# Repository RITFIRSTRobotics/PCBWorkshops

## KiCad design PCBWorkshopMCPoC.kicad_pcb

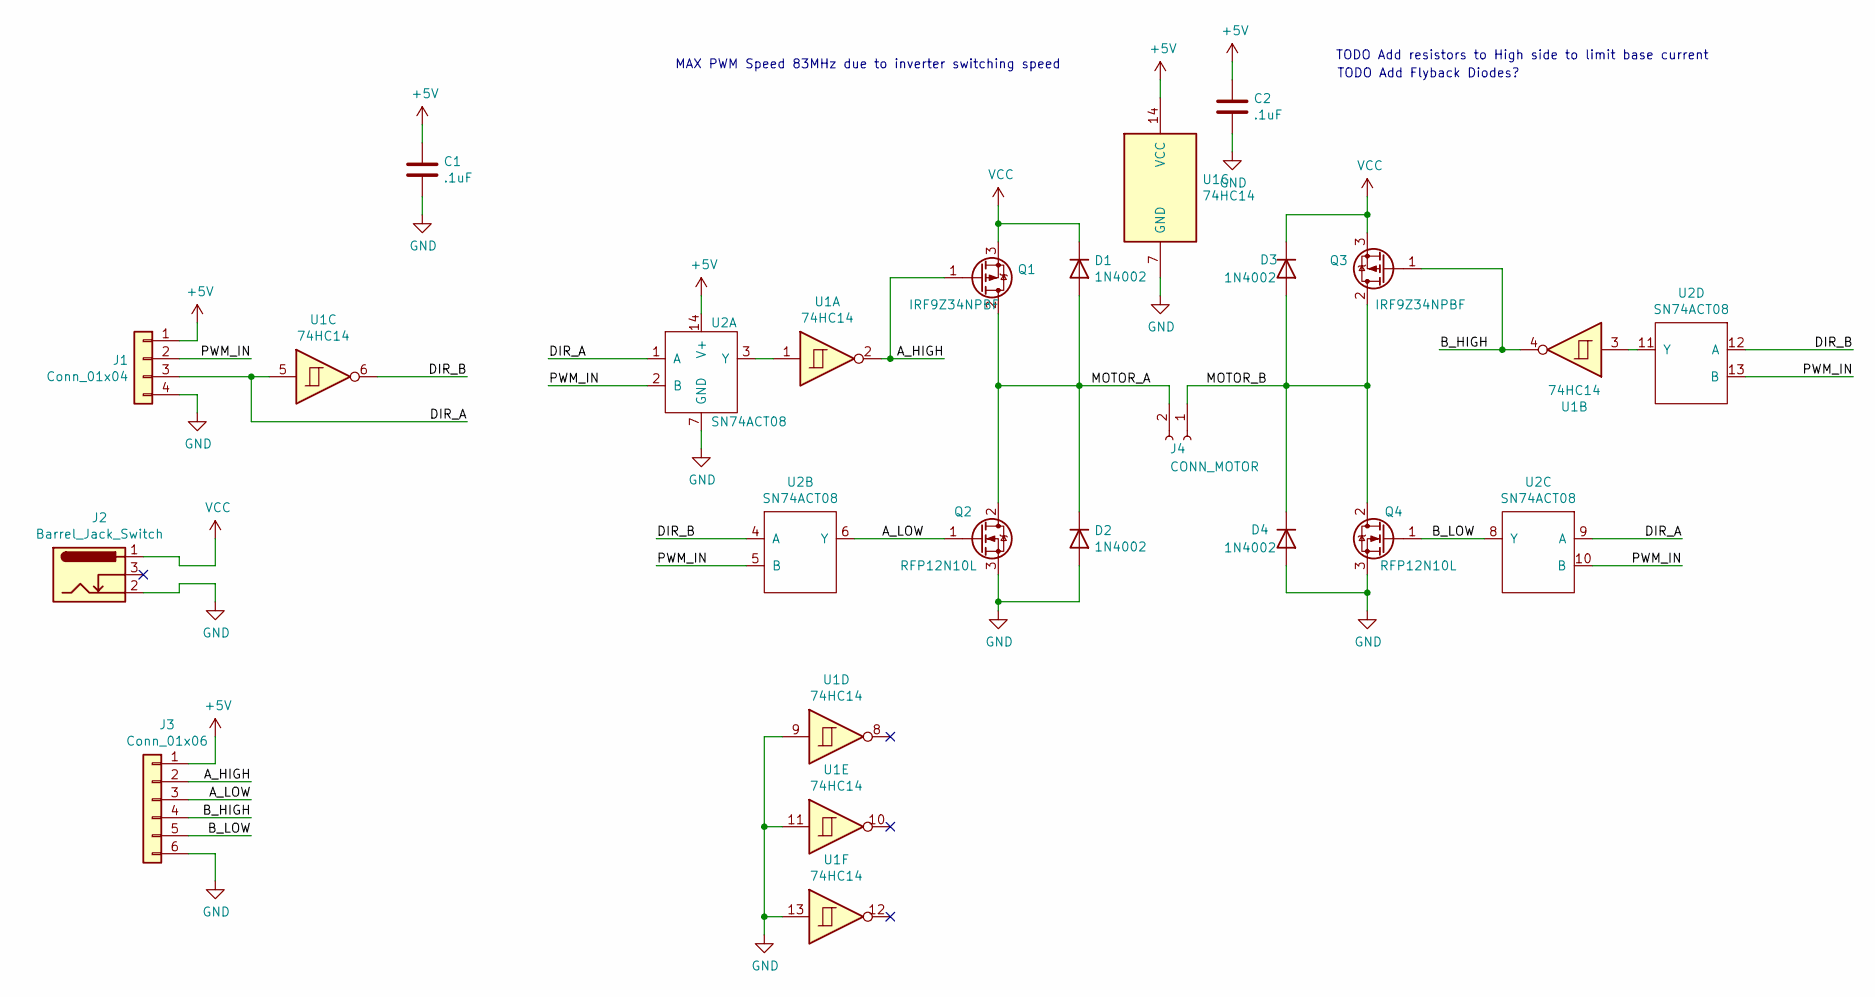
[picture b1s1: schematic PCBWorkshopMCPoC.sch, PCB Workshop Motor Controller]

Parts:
C1, C2: .1uF; C_Disc_D5.0mm_W2.5mm_P2.50mm
D1, D2, D3, D4: 1N4002; D_DO-41_SOD81_P5.08mm_Vertical_AnodeUp
J1: Conn_01x04; PinHeader_1x04_P2.54mm_Vertical
J2: Barrel_Jack_Switch; BarrelJack_Horizontal
J3: Conn_01x06; PinHeader_1x06_P2.54mm_Vertical
J4: CONN_MOTOR; PinHeader_1x02_P2.54mm_Vertical
Q1, Q3: IRF9Z34NPBF; TO-220-3_Vertical
Q2, Q4: RFP12N10L; TO-220-3_Vertical
U1: 74HC14; DIP-14_W7.62mm_Socket
U2: SN74ACT08; DIP-14_W7.62mm_Socket

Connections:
+5V: C1.1, C2.1, J1.1, J3.1, U1.14 (VCC), U2.14 (V+)
/A_HIGH: J3.2, Q1.1 (G), U1.2
/A_LOW: J3.3, Q2.1 (G), U2.6 (Y)
/B_HIGH: J3.4, Q3.1 (G), U1.4
/B_LOW: J3.5, Q4.1 (G), U2.8 (Y)
/DIR_A: J1.3, U1.5, U2.1 (A), U2.9 (A)
/DIR_B: U1.6, U2.4 (A), U2.12 (A)
/MOTOR_A: D1.2 (A), D2.1 (K), J4.2, Q1.2 (D), Q2.2 (D)
/MOTOR_B: D3.2 (A), D4.1 (K), J4.1, Q3.2 (D), Q4.2 (D)
/PWM_IN: J1.2, U2.2 (B), U2.5 (B), U2.10 (B), U2.13 (B)
GND: C1.2, C2.2, D2.2 (A), D4.2 (A), J1.4, J2.2, J3.6, Q2.3 (S), Q4.3 (S), U1.7 (GND), U1.9, U1.11, U1.13, U2.7 (GND)
unnamed: U1.1, U2.3 (Y)
unnamed: U1.3, U2.11 (Y)
VCC: D1.1 (K), D3.1 (K), J2.1, Q1.3 (S), Q3.3 (S)

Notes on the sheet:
MAX PWM Speed 83MHz due to inverter switching speed
TODO Add resistors to High side to limit base current
TODO Add Flyback Diodes?

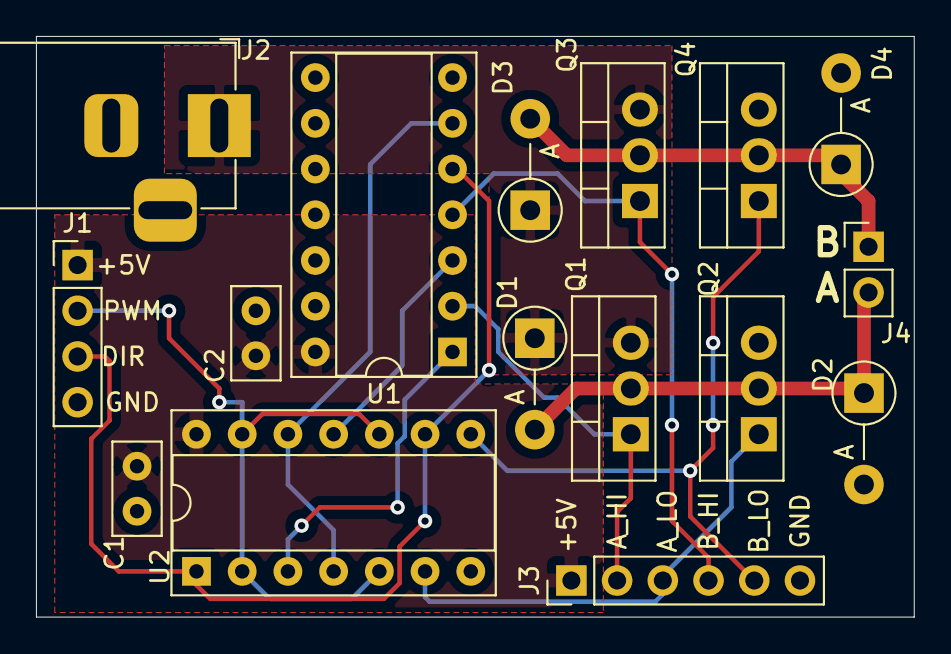
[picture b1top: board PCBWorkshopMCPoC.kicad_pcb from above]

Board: 2 copper layers, 48.8 x 32.3 mm, 16 parts (0 on the bottom side), 14 nets.

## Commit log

2021-02-12 Initial commit from initial state of workshop files
